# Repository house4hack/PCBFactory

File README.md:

# PCBFactory
Our PCB Factory to be ;)

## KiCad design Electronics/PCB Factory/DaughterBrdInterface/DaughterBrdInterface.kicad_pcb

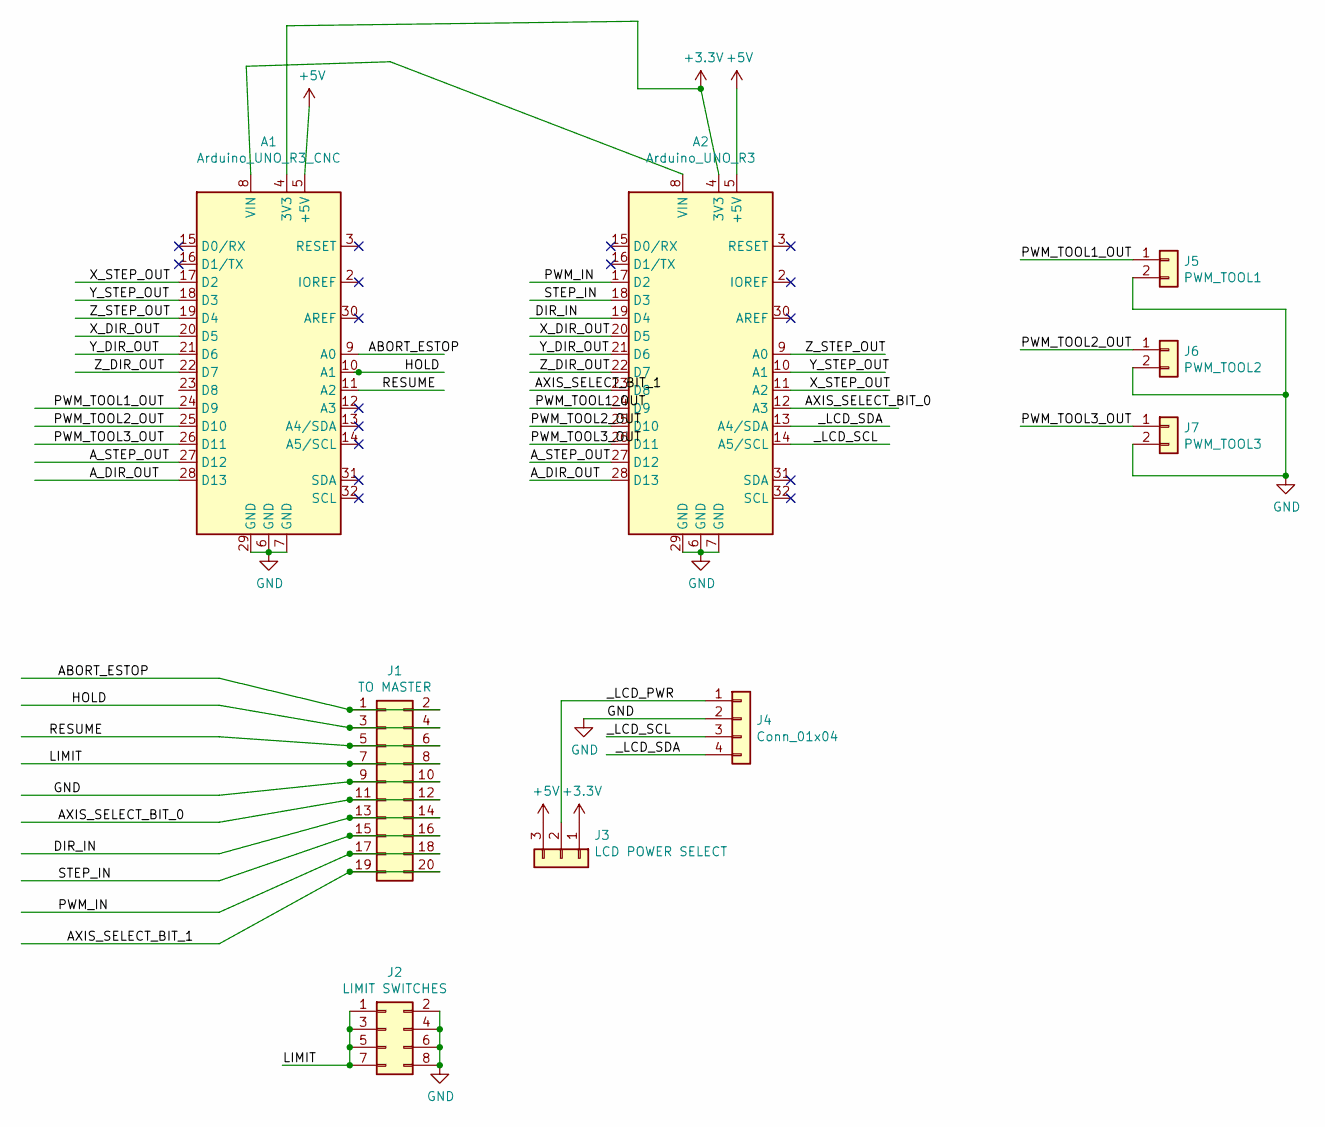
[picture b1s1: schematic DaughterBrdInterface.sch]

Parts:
A1: Arduino_UNO_R3_CNC; Arduino_UNO_R3
A2: Arduino_UNO_R3
J1: TO MASTER; PinHeader_2x10_P2.54mm_Vertical
J2: LIMIT SWITCHES; PinHeader_2x04_P2.54mm_Vertical
J3: LCD POWER SELECT; PinHeader_1x03_P2.54mm_Vertical
J4: Conn_01x04; PinHeader_1x04_P2.54mm_Vertical
J5: PWM_TOOL1; PinHeader_1x02_P2.54mm_Vertical
J6: PWM_TOOL2; PinHeader_1x02_P2.54mm_Vertical
J7: PWM_TOOL3; PinHeader_1x02_P2.54mm_Vertical

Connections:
+3V3: A1.4 (3V3), A2.4 (3V3), J3.1
+5V: A1.5 (+5V), A2.5 (+5V), J3.3
/ABORT_ESTOP: A1.9 (A0), J1.1, J1.2
/AXIS_SELECT_BIT_0: A2.12 (A3), J1.11, J1.12
/AXIS_SELECT_BIT_1: A2.23 (D8), J1.19, J1.20
/A_DIR_OUT: A1.28 (D13), A2.28 (D13)
/A_STEP_OUT: A1.27 (D12), A2.27 (D12)
/DIR_IN: A2.19 (D4), J1.13, J1.14
/HOLD: A1.10 (A1), J1.3, J1.4
/LIMIT: J1.7, J1.8, J2.1, J2.3, J2.5, J2.7
/PWM_IN: A2.17 (D2), J1.17, J1.18
/PWM_TOOL1_OUT: A1.24 (D9), A2.24 (D9), J5.1
/PWM_TOOL2_OUT: A1.25 (D10), A2.25 (D10), J6.1
/PWM_TOOL3_OUT: A1.26 (D11), A2.26 (D11), J7.1
/RESUME: A1.11 (A2), J1.5, J1.6
/STEP_IN: A2.18 (D3), J1.15, J1.16
/X_DIR_OUT: A1.20 (D5), A2.20 (D5)
/X_STEP_OUT: A1.17 (D2), A2.11 (A2)
/Y_DIR_OUT: A1.21 (D6), A2.21 (D6)
/Y_STEP_OUT: A1.18 (D3), A2.10 (A1)
/Z_DIR_OUT: A1.22 (D7), A2.22 (D7)
/Z_STEP_OUT: A1.19 (D4), A2.9 (A0)
/_LCD_PWR: J3.2, J4.1
/_LCD_SCL: A2.14 (A5/SCL), J4.3
/_LCD_SDA: A2.13 (A4/SDA), J4.4
GND: A1.6 (GND), A1.7 (GND), A1.29 (GND), A2.6 (GND), A2.7 (GND), A2.29 (GND), J1.9, J1.10, J2.2, J2.4, J2.6, J2.8, J4.2, J5.2, J6.2, J7.2
unnamed: A1.8 (VIN), A2.8 (VIN)

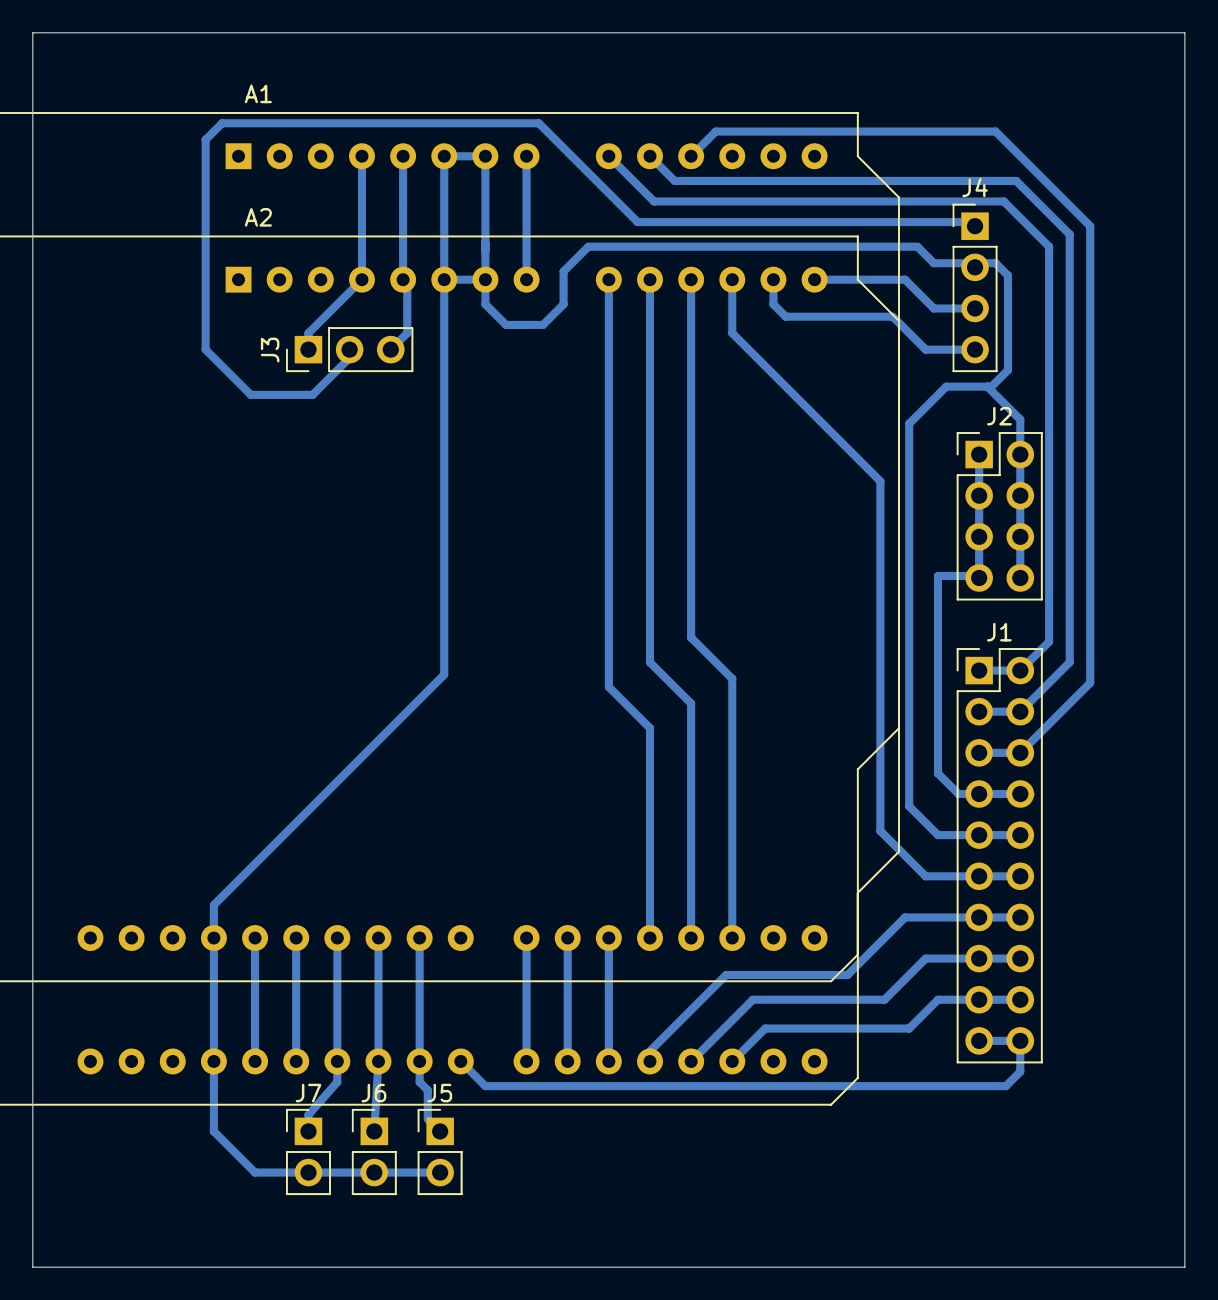
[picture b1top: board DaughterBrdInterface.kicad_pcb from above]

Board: 2 copper layers, 71.1 x 76.2 mm, 9 parts (0 on the bottom side), 27 nets.

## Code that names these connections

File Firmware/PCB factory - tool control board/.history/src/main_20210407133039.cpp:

#include <Arduino.h>

// PCB Factory - Tool control board
// using Pronteer.nz Grbl CNC shield v 3.00 clone




// ================================================
// INTERFACE TO GRBL CNC CONTROLLER
// ================================================

// the below pins are connected to the Grbl cnc controller board

// NOTE : Not reading individual limit pins into the tool controller
// as these are all connected in parallel, and echoing them to the main
// grbl controller can be done by connecting these DIRECTLY to the z-axis
// limit input on the main board.

// INPUTS ================

#define PWM_IN 2      // interupt pin
#define STEP_IN 3     // interupt pin
#define DIR_IN 4
#define AXIS_SELECT_BIT_0 A3
#define AXIS_SELECT_BIT_1 8

// OUTPUTS

#define X_DIR_OUT 5
#define Y_DIR_OUT 6
#define Z_DIR_OUT 7
#define PWM_TOOL_1_OUT  9
#define PWM_TOOL_2_OUT 10
#define PWM_TOOL_3_OUT 11
#define A_STEP_OUT 12
#define A_DIR_OUT  13

#define Z_STEP_OUT A0
#define Y_STEP_OUT A1
#define X_STEP_OUT A2

#define LCD_SDA  A4
#define LCD_SCL  A5

// STATE ==============================================

#define ACTIVE_MOTOR_GANTRY 0
#define ACTIVE_MOTOR_TOOL_1 1
#define ACTIVE_MOTOR_TOOL_2 2
#define ACTIVE_MOTOR_TOOL_3 3


// DEFINE what the "off" or unselected states are for the PWM outputs
#define PWM_INACTIVE  LOW

// default start up
int activeMotor, oldActiveMotor = ACTIVE_MOTOR_GANTRY;



void setup() {
  // put your setup code here, to run once:

  Serial.begin(115200);
  Serial.println("Connected");



  // inputs ========================================

  pinMode(STEP_IN, INPUT);
  pinMode(DIR_IN, INPUT);
  pinMode(EN_IN, INPUT);

  pinMode(PWM_IN, INPUT);

  pinMode(AXIS_SELECT_BIT_0, INPUT_PULLUP); // need to set the invert pin for COOLANT_MIST in grbl config.h
  pinMode(AXIS_SELECT_BIT_1, INPUT_PULLUP); // need to set the invert pin for COOLANT_FLOOD in grbl config.h

  // outputs  =======================================
  pinMode(PWM_TOOL_1, OUTPUT);
  pinMode(PWM_TOOL_2, OUTPUT);
  pinMode(PWM_TOOL_3, OUTPUT);

  //steppers
  pinMode(GANTRY_STEP, OUTPUT);
  pinMode(GANTRY_DIR, OUTPUT);

  pinMode(TOOL_1_STEP, OUTPUT);
  pinMode(TOOL_1_DIR, OUTPUT);

  pinMode(TOOL_2_STEP, OUTPUT);
  pinMode(TOOL_2_DIR, OUTPUT);

  pinMode(TOOL_3_STEP, OUTPUT);
  pinMode(TOOL_3_DIR, OUTPUT);


  // Read Motor select pins =========================
  getActiveMotor();

}

void getActiveMotor(){
  if (digitalRead(AXIS_SELECT_BIT_0) == HIGH) {
    if(digitalRead(AXIS_SELECT_BIT_1) == HIGH){
      activeMotor = ACTIVE_MOTOR_GANTRY;

    }else{
      activeMotor = ACTIVE_MOTOR_TOOL_1;
    }
  } else {
    if(digitalRead(AXIS_SELECT_BIT_1) == HIGH){
      activeMotor = ACTIVE_MOTOR_TOOL_3;
    }else{
      activeMotor = ACTIVE_MOTOR_TOOL_2;
    }
  }
  if(oldActiveMotor != activeMotor){
    switch (acttveMotor)
    {
      case ACTIVE_MOTOR_GANTRY:
        Serial.println("ACTIVE : GANTRY  DAUGHTER X ");
      break;
      case ACTIVE_MOTOR_TOOL_1:
      Serial.println("ACTIVE : TOOL 1  DAUGHTER Y ");
      break;
      case ACTIVE_MOTOR_TOOL_2:
      Serial.println("ACTIVE : TOOL 2 DAUGHTER Z");
      break;
      case ACTIVE_MOTOR_TOOL_3:
      Serial.println("ACTIVE : TOOL 3 DAUGHTER A ");
      break;
    }
    oldActiveMotor = activeMotor;
  }



}

void loop() {
  // put your main code here, to run repeatedly:

  // TODO: change stepper echo to use pin change interupt

  // TODO: Phase 2 -

  getActiveMotor();

  int stp = digitalRead(STEP_IN);
  int dir = digitalRead(DIR_IN);
  int pwm = digitalRead(PWM_IN);

  // enable pins on drivers are all joined to pin D8 on the shield
  digitalWrite(MOTOR_EN, digitalRead(EN_IN));

  switch(activeMotor){
    case ACTIVE_MOTOR_GANTRY:
      digitalWrite(GANTRY_STEP, stp);
      digitalWrite(GANTRY_DIR, dir);
      digitalWrite(PWM_TOOL_1, PWM_INACTIVE);
      digitalWrite(PWM_TOOL_2, PWM_INACTIVE);
      digitalWrite(PWM_TOOL_3, PWM_INACTIVE);

    break;
    case ACTIVE_MOTOR_TOOL_1:
      digitalWrite(TOOL_1_STEP, stp);
      digitalWrite(TOOL_1_DIR, dir);
      digitalWrite(PWM_TOOL_1, pwm);
      digitalWrite(PWM_TOOL_2, PWM_INACTIVE);
      digitalWrite(PWM_TOOL_3, PWM_INACTIVE);

    break;
    case ACTIVE_MOTOR_TOOL_2:
      digitalWrite(TOOL_2_STEP, stp);
      digitalWrite(TOOL_2_DIR, dir);
      digitalWrite(PWM_TOOL_2, pwm);
      digitalWrite(PWM_TOOL_1, PWM_INACTIVE);
      digitalWrite(PWM_TOOL_3, PWM_INACTIVE);

    break;
    case ACTIVE_MOTOR_TOOL_3:
      digitalWrite(TOOL_3_STEP, stp);
      digitalWrite(TOOL_3_DIR, dir);
      digitalWrite(PWM_TOOL_3, pwm);
      digitalWrite(PWM_TOOL_1, PWM_INACTIVE);
      digitalWrite(PWM_TOOL_2, PWM_INACTIVE);

    break;
  }

}

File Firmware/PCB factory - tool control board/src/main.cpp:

#include <Arduino.h>

// PCB Factory - Tool control board
// using Pronteer.nz Grbl CNC shield v 3.00 clone




// ================================================
// INTERFACE TO GRBL CNC CONTROLLER
// ================================================

// the below pins are connected to the Grbl cnc controller board

// INPUT From Grbl Z Axis Step ( stepper driver step & dir pins )
#define STEP_IN A0   // abort shield pin
#define DIR_IN A1     // hold shield pin
#define EN_IN A2        //  resume pin on shield
// OUTPUT - echo of limit limit pins
// connected to Z limit switch input on grbl controller.

// NOTE : Not reading individual limit pins into the tool controller
// as these are all connected in parallel, and echoing them to the main
// grbl controller can be done by connecting these DIRECTLY to the z-axis
// limit input on the main board.

// INPUT Axis Select (chip select) pins
#define AXIS_SELECT_BIT_0 A3  //  coolant enable pin on shield - - Connected to A3 (Coolant Mist M7)
#define AXIS_SELECT_BIT_1 A4    // SDA pin on shield -   Connected to A4 (Coolant Flood M8)

// PWM Input from Grbl
#define PWM_IN A5     // SCL pin on shield -  connected to pwm output pin on GRBL controller




// ================================================
// INTERFACE TO TOOLS / GANTRY
// ================================================

// PWM OUTPUT ECHO
#define PWM_TOOL_1  11  //  Digital pin 11 - Z limit pin on Shield
#define PWM_TOOL_2  10  //  Digital pin 10 - Y limit pin on Shield
#define PWM_TOOL_3  9   //  Digital pin 9 - X limit pin on Shield

// OUTPUTS TO STEPPER MOTORS
#define MOTOR_EN 8

// X AXIS == GANTRY MOTOR
#define GANTRY_STEP 2
#define GANTRY_DIR  5
// Y AXIS == TOOL 1 MOTOR
#define TOOL_1_STEP 3
#define TOOL_1_DIR  6
// Z AXIS == TOOL 2 MOTOR
#define TOOL_2_STEP 3
#define TOOL_2_DIR  7
// A AXIS == TOOL 3 MOTOR
#define TOOL_3_STEP 12
#define TOOL_3_DIR  13


#define ACTIVE_MOTOR_GANTRY 0
#define ACTIVE_MOTOR_TOOL_1 1
#define ACTIVE_MOTOR_TOOL_2 2
#define ACTIVE_MOTOR_TOOL_3 3


// DEFINE what the "off" or unselected states are for the PWM outputs
#define PWM_INACTIVE  LOW

int activeMotor = ACTIVE_MOTOR_GANTRY;


void setup() {
  // put your setup code here, to run once:
  // inputs ========================================

  pinMode(STEP_IN, INPUT);
  pinMode(DIR_IN, INPUT);
  pinMode(EN_IN, INPUT);

  pinMode(PWM_IN, INPUT);

  pinMode(AXIS_SELECT_BIT_0, INPUT_PULLUP); // need to set the invert pin for COOLANT_MIST in grbl config.h
  pinMode(AXIS_SELECT_BIT_1, INPUT_PULLUP); // need to set the invert pin for COOLANT_FLOOD in grbl config.h

  // outputs  =======================================
  pinMode(PWM_TOOL_1, OUTPUT);
  pinMode(PWM_TOOL_2, OUTPUT);
  pinMode(PWM_TOOL_3, OUTPUT);

  //steppers
  pinMode(GANTRY_STEP, OUTPUT);
  pinMode(GANTRY_DIR, OUTPUT);

  pinMode(TOOL_1_STEP, OUTPUT);
  pinMode(TOOL_1_DIR, OUTPUT);

  pinMode(TOOL_2_STEP, OUTPUT);
  pinMode(TOOL_2_DIR, OUTPUT);

  pinMode(TOOL_3_STEP, OUTPUT);
  pinMode(TOOL_3_DIR, OUTPUT);


  // Read Motor select pins =========================
  getActiveMotor();

}

void getActiveMotor(){
  if (digitalRead(AXIS_SELECT_BIT_0) == HIGH) {
    if(digitalRead(AXIS_SELECT_BIT_1) == HIGH){
      activeMotor = ACTIVE_MOTOR_GANTRY;
    }else{
      activeMotor = ACTIVE_MOTOR_TOOL_1;
    }
  } else {
    if(digitalRead(AXIS_SELECT_BIT_1) == HIGH){
      activeMotor = ACTIVE_MOTOR_TOOL_3;
    }else{
      activeMotor = ACTIVE_MOTOR_TOOL_2;
    }
  }
}

void loop() {
  // put your main code here, to run repeatedly:

  // TODO: change stepper echo to use pin change interupt

  // TODO: Phase 2 -

  getActiveMotor();

  int stp = digitalRead(STEP_IN);
  int dir = digitalRead(DIR_IN);
  int pwm = digitalRead(PWM_IN);

  // enable pins on drivers are all joined to pin D8 on the shield
  digitalWrite(MOTOR_EN, digitalRead(EN_IN));

  switch(activeMotor){
    case ACTIVE_MOTOR_GANTRY:
      digitalWrite(GANTRY_STEP, stp);
      digitalWrite(GANTRY_DIR, dir);
      digitalWrite(PWM_TOOL_1, PWM_INACTIVE);
      digitalWrite(PWM_TOOL_2, PWM_INACTIVE);
      digitalWrite(PWM_TOOL_3, PWM_INACTIVE);

    break;
    case ACTIVE_MOTOR_TOOL_1:
      digitalWrite(TOOL_1_STEP, stp);
      digitalWrite(TOOL_1_DIR, dir);
      digitalWrite(PWM_TOOL_1, pwm);
      digitalWrite(PWM_TOOL_2, PWM_INACTIVE);
      digitalWrite(PWM_TOOL_3, PWM_INACTIVE);

    break;
    case ACTIVE_MOTOR_TOOL_2:
      digitalWrite(TOOL_2_STEP, stp);
      digitalWrite(TOOL_2_DIR, dir);
      digitalWrite(PWM_TOOL_2, pwm);
      digitalWrite(PWM_TOOL_1, PWM_INACTIVE);
      digitalWrite(PWM_TOOL_3, PWM_INACTIVE);

    break;
    case ACTIVE_MOTOR_TOOL_3:
      digitalWrite(TOOL_3_STEP, stp);
      digitalWrite(TOOL_3_DIR, dir);
      digitalWrite(PWM_TOOL_3, pwm);
      digitalWrite(PWM_TOOL_1, PWM_INACTIVE);
      digitalWrite(PWM_TOOL_2, PWM_INACTIVE);

    break;
  }

}

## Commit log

2021-03-06 First seeds being planted :)
2021-03-10 Updated GRBL Config Change LOG
2021-03-11 added Firmware folder, added to readme
2021-03-11 added Firmware folder
2021-03-14 Added some 3d printed parts we created.
2021-03-14 changed readme
2021-03-14 trying to get line feeds working in code blocks
2021-03-14 trying to get line feeds working in code blocks 2
2021-03-14 trying to get line feeds working in code blocks 3
2021-03-14 added wiring Schematic
2021-03-14 correct spelling
2021-03-14 correct spelling - again !
2021-03-14 moved into folder
2021-03-18 added Tool Control initial Code
2021-03-23 Added .vscode to gitignore
2021-04-01 added wiring diagram
2021-04-04 moved wiring diagram to electronics
2021-04-04 added Draft Daughter Board
2021-04-20 updated Daughter to Mega2560
2023-03-15 Romoved File
